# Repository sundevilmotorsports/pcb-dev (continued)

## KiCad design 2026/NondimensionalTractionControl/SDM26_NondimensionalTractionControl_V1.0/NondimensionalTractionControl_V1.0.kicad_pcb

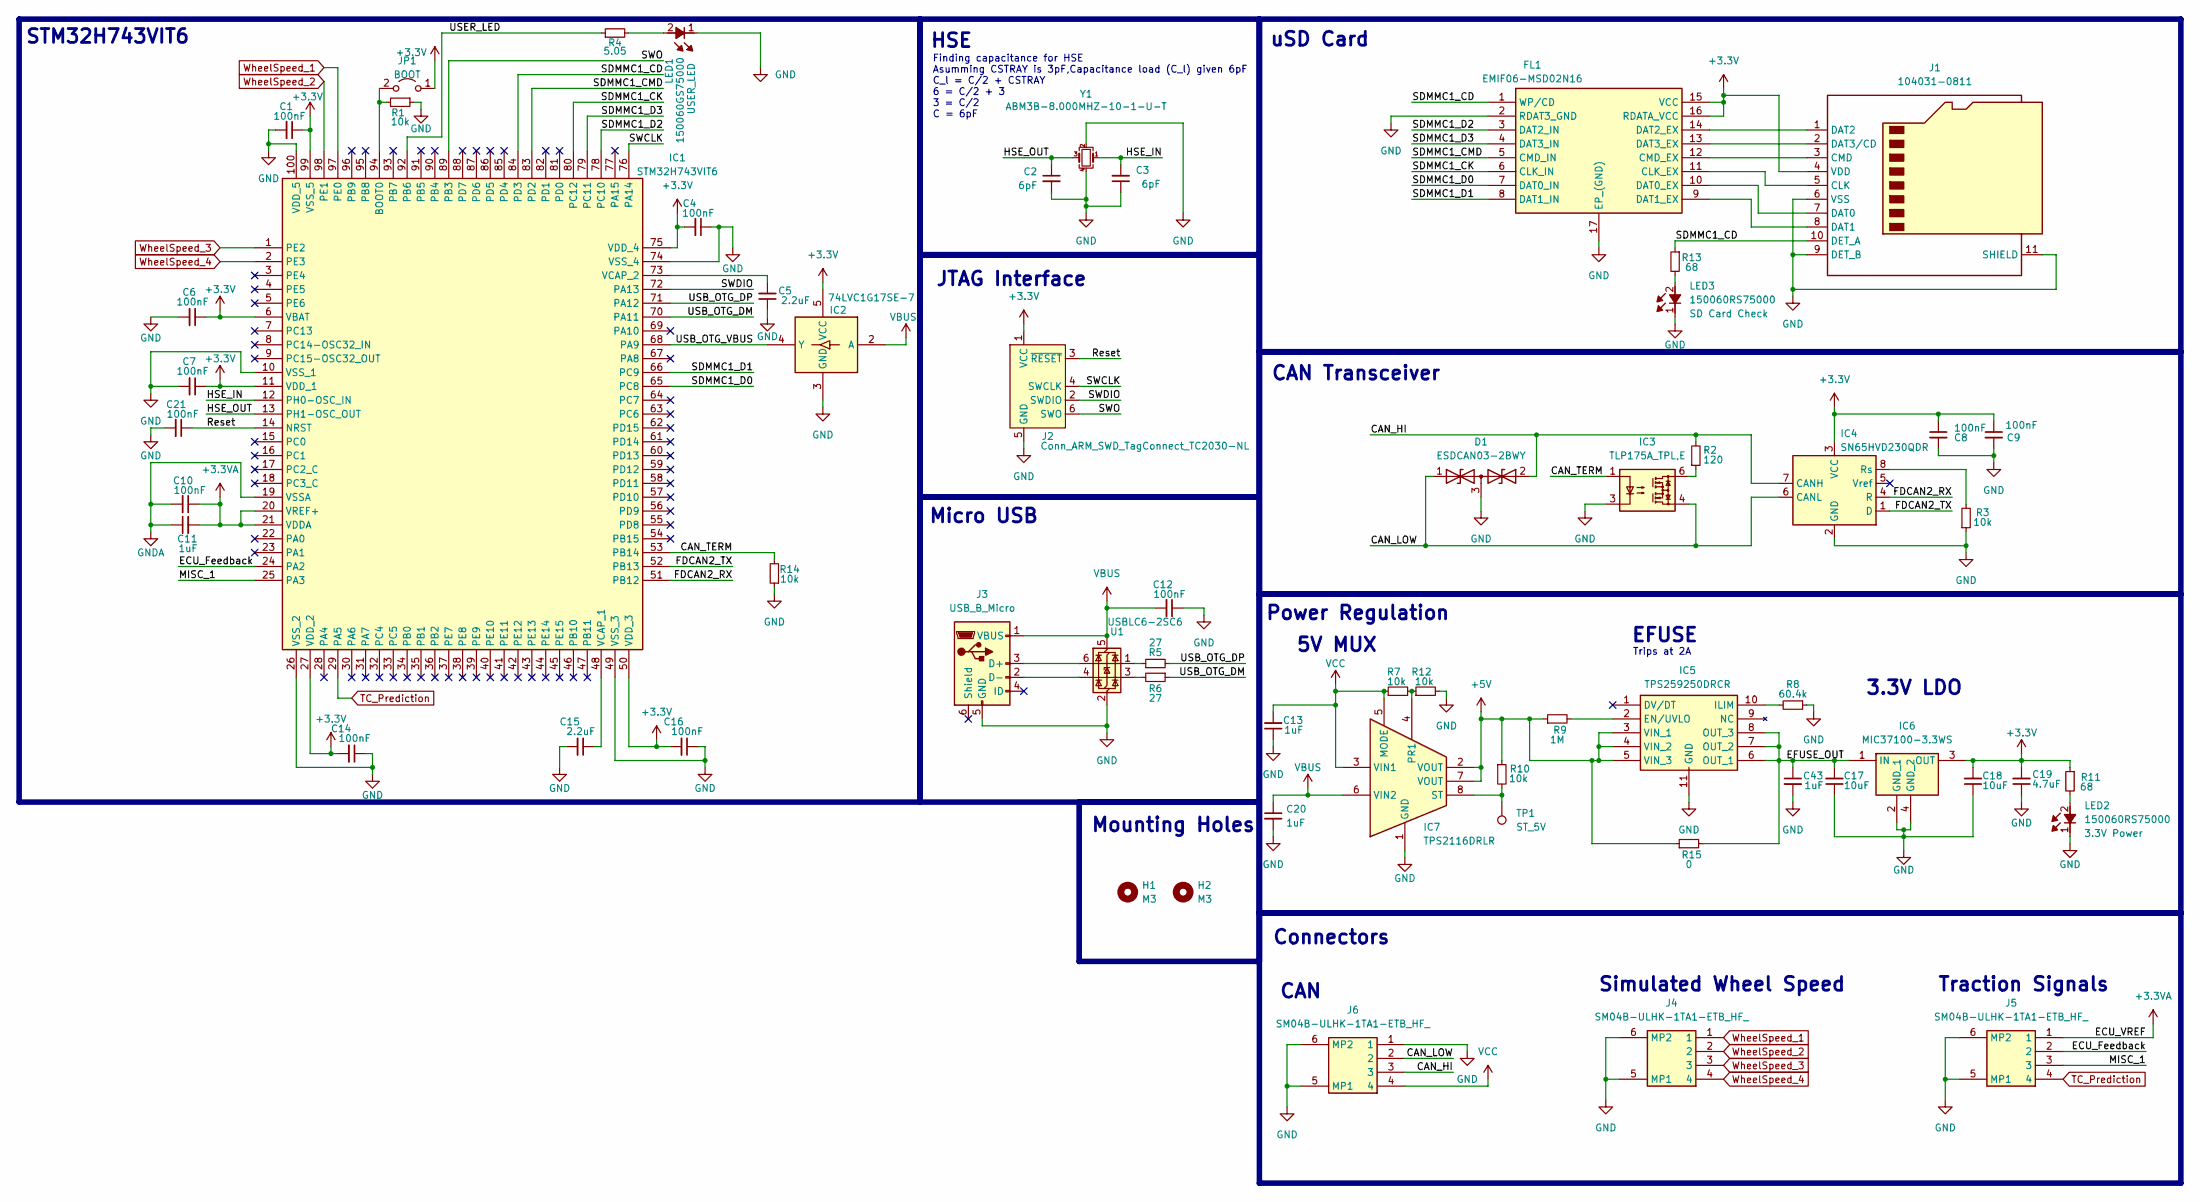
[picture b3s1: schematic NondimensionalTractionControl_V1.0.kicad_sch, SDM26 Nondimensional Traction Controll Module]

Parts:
C1, C4, C6, C7, C8, C9, C10, C12, C14, C16, C21: 100nF; C_0603_1608Metric
C2, C3: 6pF; C_0603_1608Metric
C5, C15: 2.2uF; C_0603_1608Metric
C11, C13, C20, C43: 1uF; C_0603_1608Metric
C17, C18: 10uF; C_0603_1608Metric
C19: 4.7uF; C_0603_1608Metric
D1: ESDCAN03-2BWY; SOT65P210X110-3N; Mouser Part Number 511-ESDCAN03-2BWY
FL1: EMIF06-MSD02N16; EMIF06MSD02N16; Mouser Part Number 511-EMIF06-MSD02N16
H1, H2: M3; MountingHole_3.2mm_M3
IC1: STM32H743VIT6; QFP50P1600X1600X160-100L; Mouser Part Number 511-STM32H743VIT6
IC2: 74LVC1G17SE-7; SOT65P210X110-5L; Mouser Part Number 621-74LVC1G17SE-7
IC3: TLP175A_TPL,E; TLP266J; Mouser Part Number 757-TLP175A(TPLE
IC4: SN65HVD230QDR; SOIC127P600X175-8L; Mouser Part Number 595-SN65HVD230QDR
IC5: TPS259250DRCR; SON50P300X300X100-11L-D; Mouser Part Number 595-TPS259250DRCR
IC6: MIC37100-3.3WS; SOT230P700X180-4N; Mouser Part Number 998-MIC37100-3.3WS
IC7: TPS2116DRLR; SOTFL50P160X60-8L; Mouser Part Number 595-TPS2116DRLR
J1: 104031-0811; 1040310811; Mouser Part Number 538-104031-0811
J2: Conn_ARM_SWD_TagConnect_TC2030-NL; Tag-Connect_TC2030-IDC-NL_2x03_P1.27mm_Vertical
J3: USB_B_Micro; USB_Micro-B_Molex-105017-0001
J4, J5, J6: SM04B-ULHK-1TA1-ETB_HF_; SM04BULHK1TA1ETBHF; Mouser Part Number 306-SM4BULH1TA1ETBHF
JP1: BOOT; PinHeader_1x02_P2.54mm_Vertical
LED1: 150060GS75000; LEDC1608X80N; Mouser Part Number 710-150060GS75000
LED2, LED3: 150060RS75000; LEDC1608X80N; Mouser Part Number 710-150060RS75000
R1, R3, R7, R10, R12, R14: 10k; R_0603_1608Metric
R2: 120; R_0603_1608Metric
R4: 5.05; R_0603_1608Metric
R5, R6: 27; R_0603_1608Metric
R8: 60.4k; R_0603_1608Metric
R9: 1M; R_0603_1608Metric
R11, R13: 68; R_0603_1608Metric
R15: 0; R_0603_1608Metric
TP1: ST_5V; TestPoint_Pad_1.5x1.5mm
U1: USBLC6-2SC6; SOT-23-6
Y1: ABM3B-8.000MHZ-10-1-U-T; ABM3B; Mouser Part Number 815-ABM3B8MHZ101UT

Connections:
+3.3V: C1.1, C4.2, C6.1, C7.1, C8.1, C9.1, C14.2, C16.2, C18.2, C19.2, FL1.15 (VCC), FL1.16 (RDATA_VCC), IC1.6 (VBAT), IC1.11 (VDD_1), IC1.27 (VDD_2), IC1.50 (VDD_3), IC1.75 (VDD_4), IC1.99 (VSS_5), IC2.5 (VCC), IC4.3 (VCC), IC6.3 (OUT), J1.4 (VDD), J2.1 (VCC), JP1.1 (A), R11.1
+3.3VA: C10.1, C11.2, IC1.20 (VREF+), IC1.21 (VDDA), J5.1
+5V: IC5.3 (VIN_1), IC5.4 (VIN_2), IC5.5 (VIN_3), IC7.2 (VOUT), IC7.7 (VOUT), R9.1, R10.1, R15.1
/CAN_HI: D1.2, IC4.7 (CANH), J6.3, R2.2
/CAN_LOW: D1.1, IC3.4, IC4.6 (CANL), J6.2
/CAN_TERM: IC1.53 (PB14), IC3.1, R14.2
/ECU_Feedback: IC1.24 (PA2), J5.2
/EFUSE_OUT: C17.2, C43.1, IC5.6 (OUT_1), IC5.7 (OUT_2), IC5.8 (OUT_3), IC6.1 (IN), R15.2
/FDCAN2_RX: IC1.51 (PB12), IC4.4 (R)
/FDCAN2_TX: IC1.52 (PB13), IC4.1 (D)
/HSE_IN: C3.2, IC1.12 (PH0-OSC_IN), Y1.1 (XTAL_1)
/HSE_OUT: C2.1, IC1.13 (PH1-OSC_OUT), Y1.3 (XTAL_2)
/MISC_1: IC1.25 (PA3), J5.3
/Reset: C21.1, IC1.14 (NRST), J2.3 (~RESET)
/SDMMC1_CD: FL1.1 (WP/CD), IC1.84 (PD3), J1.10 (DET_A), R13.1
/SDMMC1_CK: FL1.6 (CLK_IN), IC1.80 (PC12)
/SDMMC1_CMD: FL1.5 (CMD_IN), IC1.83 (PD2)
/SDMMC1_D0: FL1.7 (DAT0_IN), IC1.65 (PC8)
/SDMMC1_D1: FL1.8 (DAT1_IN), IC1.66 (PC9)
/SDMMC1_D2: FL1.3 (DAT2_IN), IC1.78 (PC10)
/SDMMC1_D3: FL1.4 (DAT3_IN), IC1.79 (PC11)
/SWCLK: IC1.76 (PA14), J2.4 (SWCLK)
/SWDIO: IC1.72 (PA13), J2.2 (SWDIO)
/SWO: IC1.89 (PB3), J2.6 (SWO)
/USB_OTG_DM: IC1.70 (PA11), R6.1
/USB_OTG_DP: IC1.71 (PA12), R5.2
/USB_OTG_VBUS: IC1.68 (PA9), IC2.4 (Y)
/USER_LED: IC1.92 (PB6), R4.1
GND: C1.2, C2.2, C3.1, C4.1, C5.1, C6.2, C7.2, C8.2, C9.2, C12.1, C13.1, C14.1, C15.2, C16.1, C17.1, C18.1, C19.1, C20.2, C21.2, C43.2, D1.3, FL1.2 (RDAT3_GND), FL1.17 (EP_(GND)), IC1.10 (VSS_1), IC1.26 (VSS_2), IC1.49 (VSS_3), IC1.74 (VSS_4), IC1.100 (VDD_5), IC2.3 (GND), IC3.3, IC4.2 (GND), IC5.11 (GND), IC6.2 (GND_1), IC6.4 (GND_2), IC7.1 (GND), J1.6 (VSS), J1.9 (DET_B), J1.11 (SHIELD), J2.5 (GND), J3.5 (GND), J4.5 (MP1), J4.6 (MP2), J5.5 (MP1), J5.6 (MP2), J6.1, J6.5 (MP1), J6.6 (MP2), LED1.1 (K), LED2.1 (K), LED3.1 (K), R1.1, R3.1, R8.1, R12.2, R14.1, U1.2 (GND), Y1.2 (GND_1), Y1.4 (GND_2)
GNDA: C10.2, C11.1, IC1.19 (VSSA)
unnamed: FL1.11 (CLK_EX), J1.5 (CLK)
unnamed: FL1.12 (CMD_EX), J1.3 (CMD)
unnamed: FL1.10 (DAT0_EX), J1.7 (DAT0)
unnamed: FL1.9 (DAT1_EX), J1.8 (DAT1)
unnamed: FL1.14 (DAT2_EX), J1.1 (DAT2)
unnamed: FL1.13 (DAT3_EX), J1.2 (DAT3/CD)
unnamed: IC1.94 (BOOT0), JP1.2 (B), R1.2
unnamed: C15.1, IC1.48 (VCAP_1)
unnamed: C5.2, IC1.73 (VCAP_2)
unnamed: IC3.6, R2.1
unnamed: IC4.8 (Rs), R3.2
unnamed: IC5.2 (EN/UVLO), R9.2
unnamed: IC5.10 (ILIM), R8.2
unnamed: IC7.4 (PR1), R7.2, R12.1
unnamed: IC7.8 (ST), R10.2, TP1.1
unnamed: J3.3 (D+), U1.6 (I/O1)
unnamed: J3.2 (D-), U1.4 (I/O2)
unnamed: LED1.2 (A), R4.2
unnamed: LED2.2 (A), R11.2
unnamed: LED3.2 (A), R13.2
unnamed: R5.1, U1.1 (I/O1)
unnamed: R6.2, U1.3 (I/O2)
TC_Prediction: IC1.29 (PA5), J5.4
VBUS: C12.2, C20.1, IC2.2 (A), IC7.6 (VIN2), J3.1 (VBUS), U1.5 (VBUS)
VCC: C13.2, IC7.3 (VIN1), IC7.5 (MODE), J6.4, R7.1
WheelSpeed_1: IC1.97 (PE0), J4.1
WheelSpeed_2: IC1.98 (PE1), J4.2
WheelSpeed_3: IC1.1 (PE2), J4.3
WheelSpeed_4: IC1.2 (PE3), J4.4

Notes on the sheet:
HSE
Power Regulation
Traction Signals
EFUSE
Mounting Holes
Simulated Wheel Speed
STM32H743VIT6
uSD Card
CAN
Trips at 2A
CAN Transceiver
JTAG Interface
3.3V LDO
5V MUX
Finding capacitance for HSE Asumming CSTRAY is 3pF,Capacitance load (C_l) given 6pF C_l = C/2 + CSTRAY 6 = C/2 + 3 3 = C/2 C = 6pF
Connectors
Micro USB

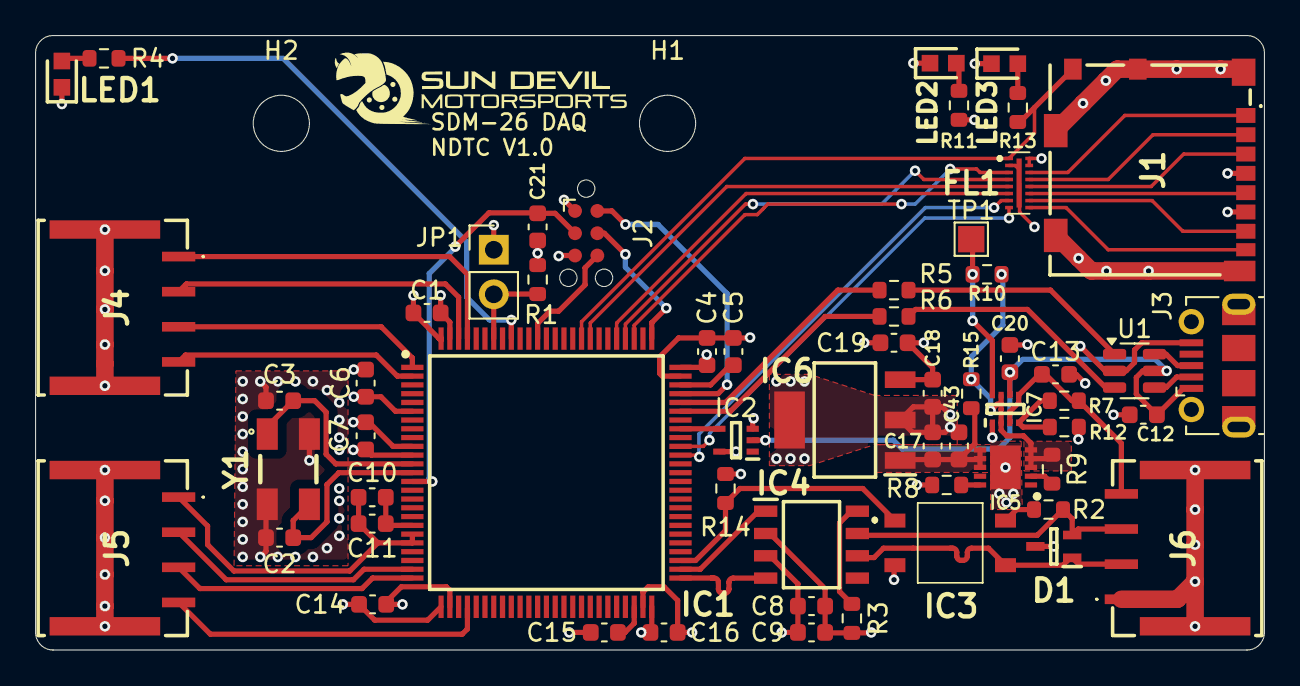
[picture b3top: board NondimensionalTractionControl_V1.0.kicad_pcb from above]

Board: 4 copper layers, 70.0 x 35.0 mm, 61 parts (0 on the bottom side), 59 nets.
